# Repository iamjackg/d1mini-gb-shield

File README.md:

# GB Link Shield

This is a shield to connect your Game Boy Pocket/Light/Color to a [Wemos D1 Mini](https://www.wemos.cc/en/latest/d1/d1_mini.html), a tiny ESP8266 board, or an [MH-ET LIVE MiniKit](https://forum.mhetlive.com/topic/8/mh-et-live-minikit-for-esp32), an ESP32 board that is pin-compatible with the D1 Mini.

The link cable connects directly to the PCB. The shield also has room for an optional resistor + 3mm LED combo. The LED will light up when a Game Boy is connected and powered on.

It can be used with a bunch of cool projects:

- [ESP32 + Phomemo T02 Game Boy Printer](https://github.com/iamjackg/esp32-phomemo-gameboy-printer)
- [NeoGB Printer](https://github.com/zenaro147/NeoGB-Printer) 
- [ESP8266 Gameboy Printer](https://github.com/applefreak/esp8266-gameboy-printer)

## Pinout

| Game Boy pin  | D1 Mini pin | MiniKit pin |
| ------------- | ------------- | ------------- |
| Ground  | Ground  | Ground |
| Vcc  | D8 (optional, see note) | GPIO5 (optional, see note) |
| Serial Out | D7 | GPIO23 |
| Serial In | D6 | GPIO19 | 
| Clock | D5 | GPIO18 |
| SD | Not connected | Not connected | 

*Vcc Note:* you can optionally bridge the `GB>D8` jumper on the shield. This will pull D8/GPIO5 high (3.3v) when a Game Boy is connected. This is **not** intended to power anything: it's just supposed to be a logic signal. Remember to set the pin to pulldown mode, or it will change state at random!

## Purchasing

You can get this made for about $8 for three copies at [OSHPark](https://oshpark.com/shared_projects/lIuomgBX). Of course, any other PCB fab will also be able to make this. Make sure the PCB is 1.6mm thick so it fits in the Game Boy cable.

## Bill of materials

Since this is just a PCB, you will need some extra components to make it work.

### Required

#### Level shifter

The Game Boy runs at 5V, but both the ESP8266 and the ESP32 use 3.3V. You will need a **level shifter** with the same footprint as the [SparkFun Logic Level Converter](https://www.sparkfun.com/products/12009).

#### Pins

Your ESP board might come with these, but you'll need **two 8-pin male headers** to solder/connect the shield to the microcontroller board. The [SparkFun 10-Pin Header](https://www.sparkfun.com/products/18221) is a good example (you can just snip off two pins).

#### Game Boy Link Cable

This board works with Game Boy Pocket/Light/Color link cables. You can find them for cheap on AliExpress, or for less cheap on Amazon. Just make sure you're not getting the Original Game Boy cable (sometimes called DMG) since it's not the same size and will not work with this shield.

### Optional

#### Resistor and LED

You can use a **330 Ohm resistor** and a **3mm LED**.

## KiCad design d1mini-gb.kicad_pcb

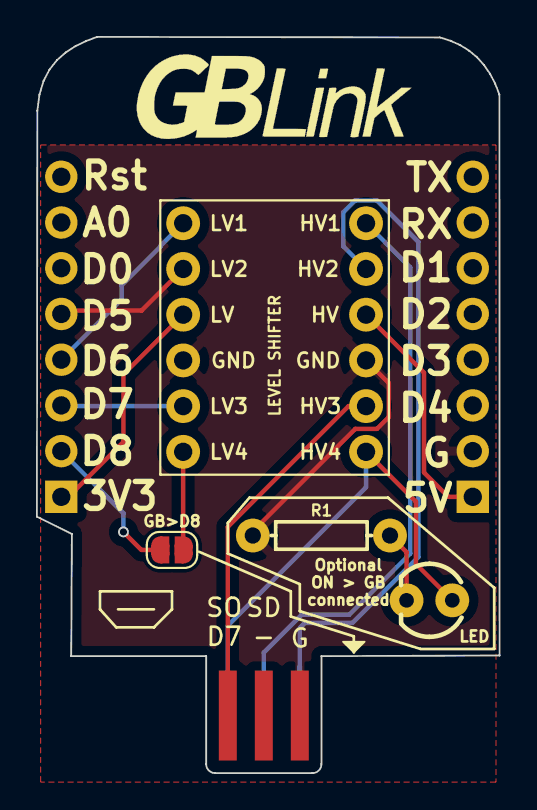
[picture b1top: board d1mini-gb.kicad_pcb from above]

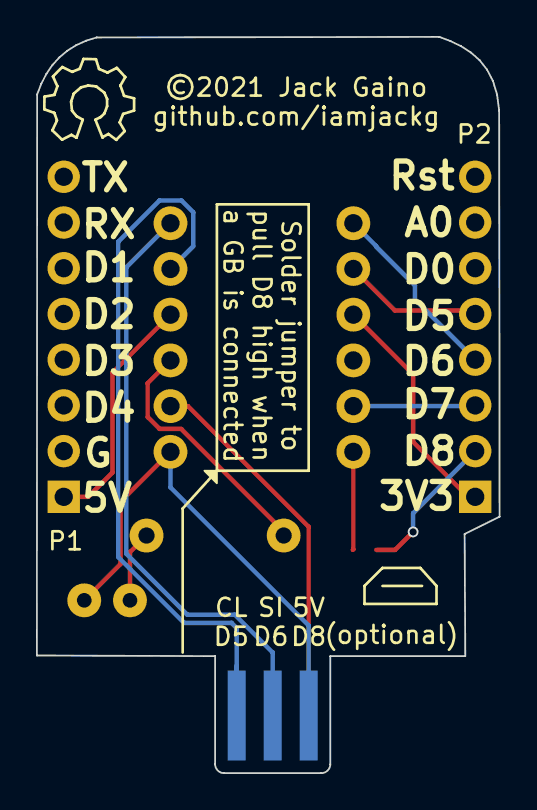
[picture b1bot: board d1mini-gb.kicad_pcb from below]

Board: 2 copper layers, 25.7 x 40.9 mm, 7 parts (2 on the bottom side), 13 nets.

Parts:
B1: LEVEL SHIFTER; SPARKFUN_LOGIC_LEVEL_CONVERTER
D1: LED3MM; LED_3MM
GB1: gb-link-socket
JP1: SolderJumper_2_Open; SolderJumper-2_P1.3mm_Open_RoundedPad1.0x1.5mm
P1, P2: CONN_01X08; D1_mini_Pin_Header
R1: 1KOHM-HORIZ-1_4W-1%; AXIAL-0.3

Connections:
/+3.3V: B1.LV, P2.1
/+5V: B1.HV, P1.1
/D5: B1.LV2, P2.5
/D6: B1.LV1, P2.4
/D7: B1.LV3, P2.3
/D8: JP1.2, P2.2
/GND: B1.GND1, B1.GND2, GB1.6, P1.2, R1.P$1
unnamed: B1.HV1, GB1.3
unnamed: B1.HV2, GB1.5
unnamed: B1.HV3, GB1.2
unnamed: B1.HV4, D1.A, GB1.1
unnamed: B1.LV4, JP1.1
unnamed: D1.K, R1.P$2

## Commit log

2022-01-14 Add OSHPark link to README.md
2022-01-14 Clarify fab instructions in README.md
2022-01-15 Updated schematics with correct pin swap

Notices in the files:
d1mini-gb.kicad_pcb:
©2021 Jack Gaino
